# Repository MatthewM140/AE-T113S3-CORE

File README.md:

# AE-T113S3-CORE

A custom **Allwinner T113-S3 core board** designed to solder onto a carrier PCB. Revision **R1.0** uses a **35 × 35 mm** footprint with **100 castellated pads** around its four edges.

## Hardware at a glance

| Feature | Details |
| --- | --- |
| Processor | Allwinner T113-S3 |
| Storage | 256 MB NAND flash |
| Module footprint | 35 × 35 mm, 100 castellated pads |
| Carrier connections | GPIO, USB, SPI0, audio, TV out, reset, reference clock, 3.3 V and ground |
| I/O voltage selection | Solder jumpers marked **PG** (3.3 V / 1.8 V) and **PE** (3.3 V / 2.8 V) |

## Design files

| File | Contents |
| --- | --- |
| [KiCad project](T113-S3_Core_V1/T113-S3_Core_V1/T113-S3_Core_V1.kicad_pro) | Open this project to browse the schematic and PCB layout. |
| [Schematic](T113-S3_Core_V1/T113-S3_Core_V1/T113-S3_Core_V1.kicad_sch) | Circuit design and signal assignments. |
| [PCB layout](T113-S3_Core_V1/T113-S3_Core_V1/T113-S3_Core_V1.kicad_pcb) | Board outline, component placement, routing, and numbered pads. |
| [KiCad libraries](libraries/) | Custom symbols, footprints, and 3D models. |
| [Fabrication archive](T113-S3_Core_V1/T113-S3_Core_V1_FAB.zip) | Gerber and drill files. [Browse the unpacked files](T113-S3_Core_V1/T113-S3_Core_V1_FAB/). |

## Carrier board integration

Start with the [100-pad carrier landing footprint](libraries/footprints.pretty/Carrier_Landing_35x35_100P.kicad_mod) in the repository. Use the schematic and PCB layout to check pad numbering, the pin 1 orientation, and the PG and PE voltage selections against your carrier design.

## PCB routing and pad labels

Click the layout image to open it at full resolution.

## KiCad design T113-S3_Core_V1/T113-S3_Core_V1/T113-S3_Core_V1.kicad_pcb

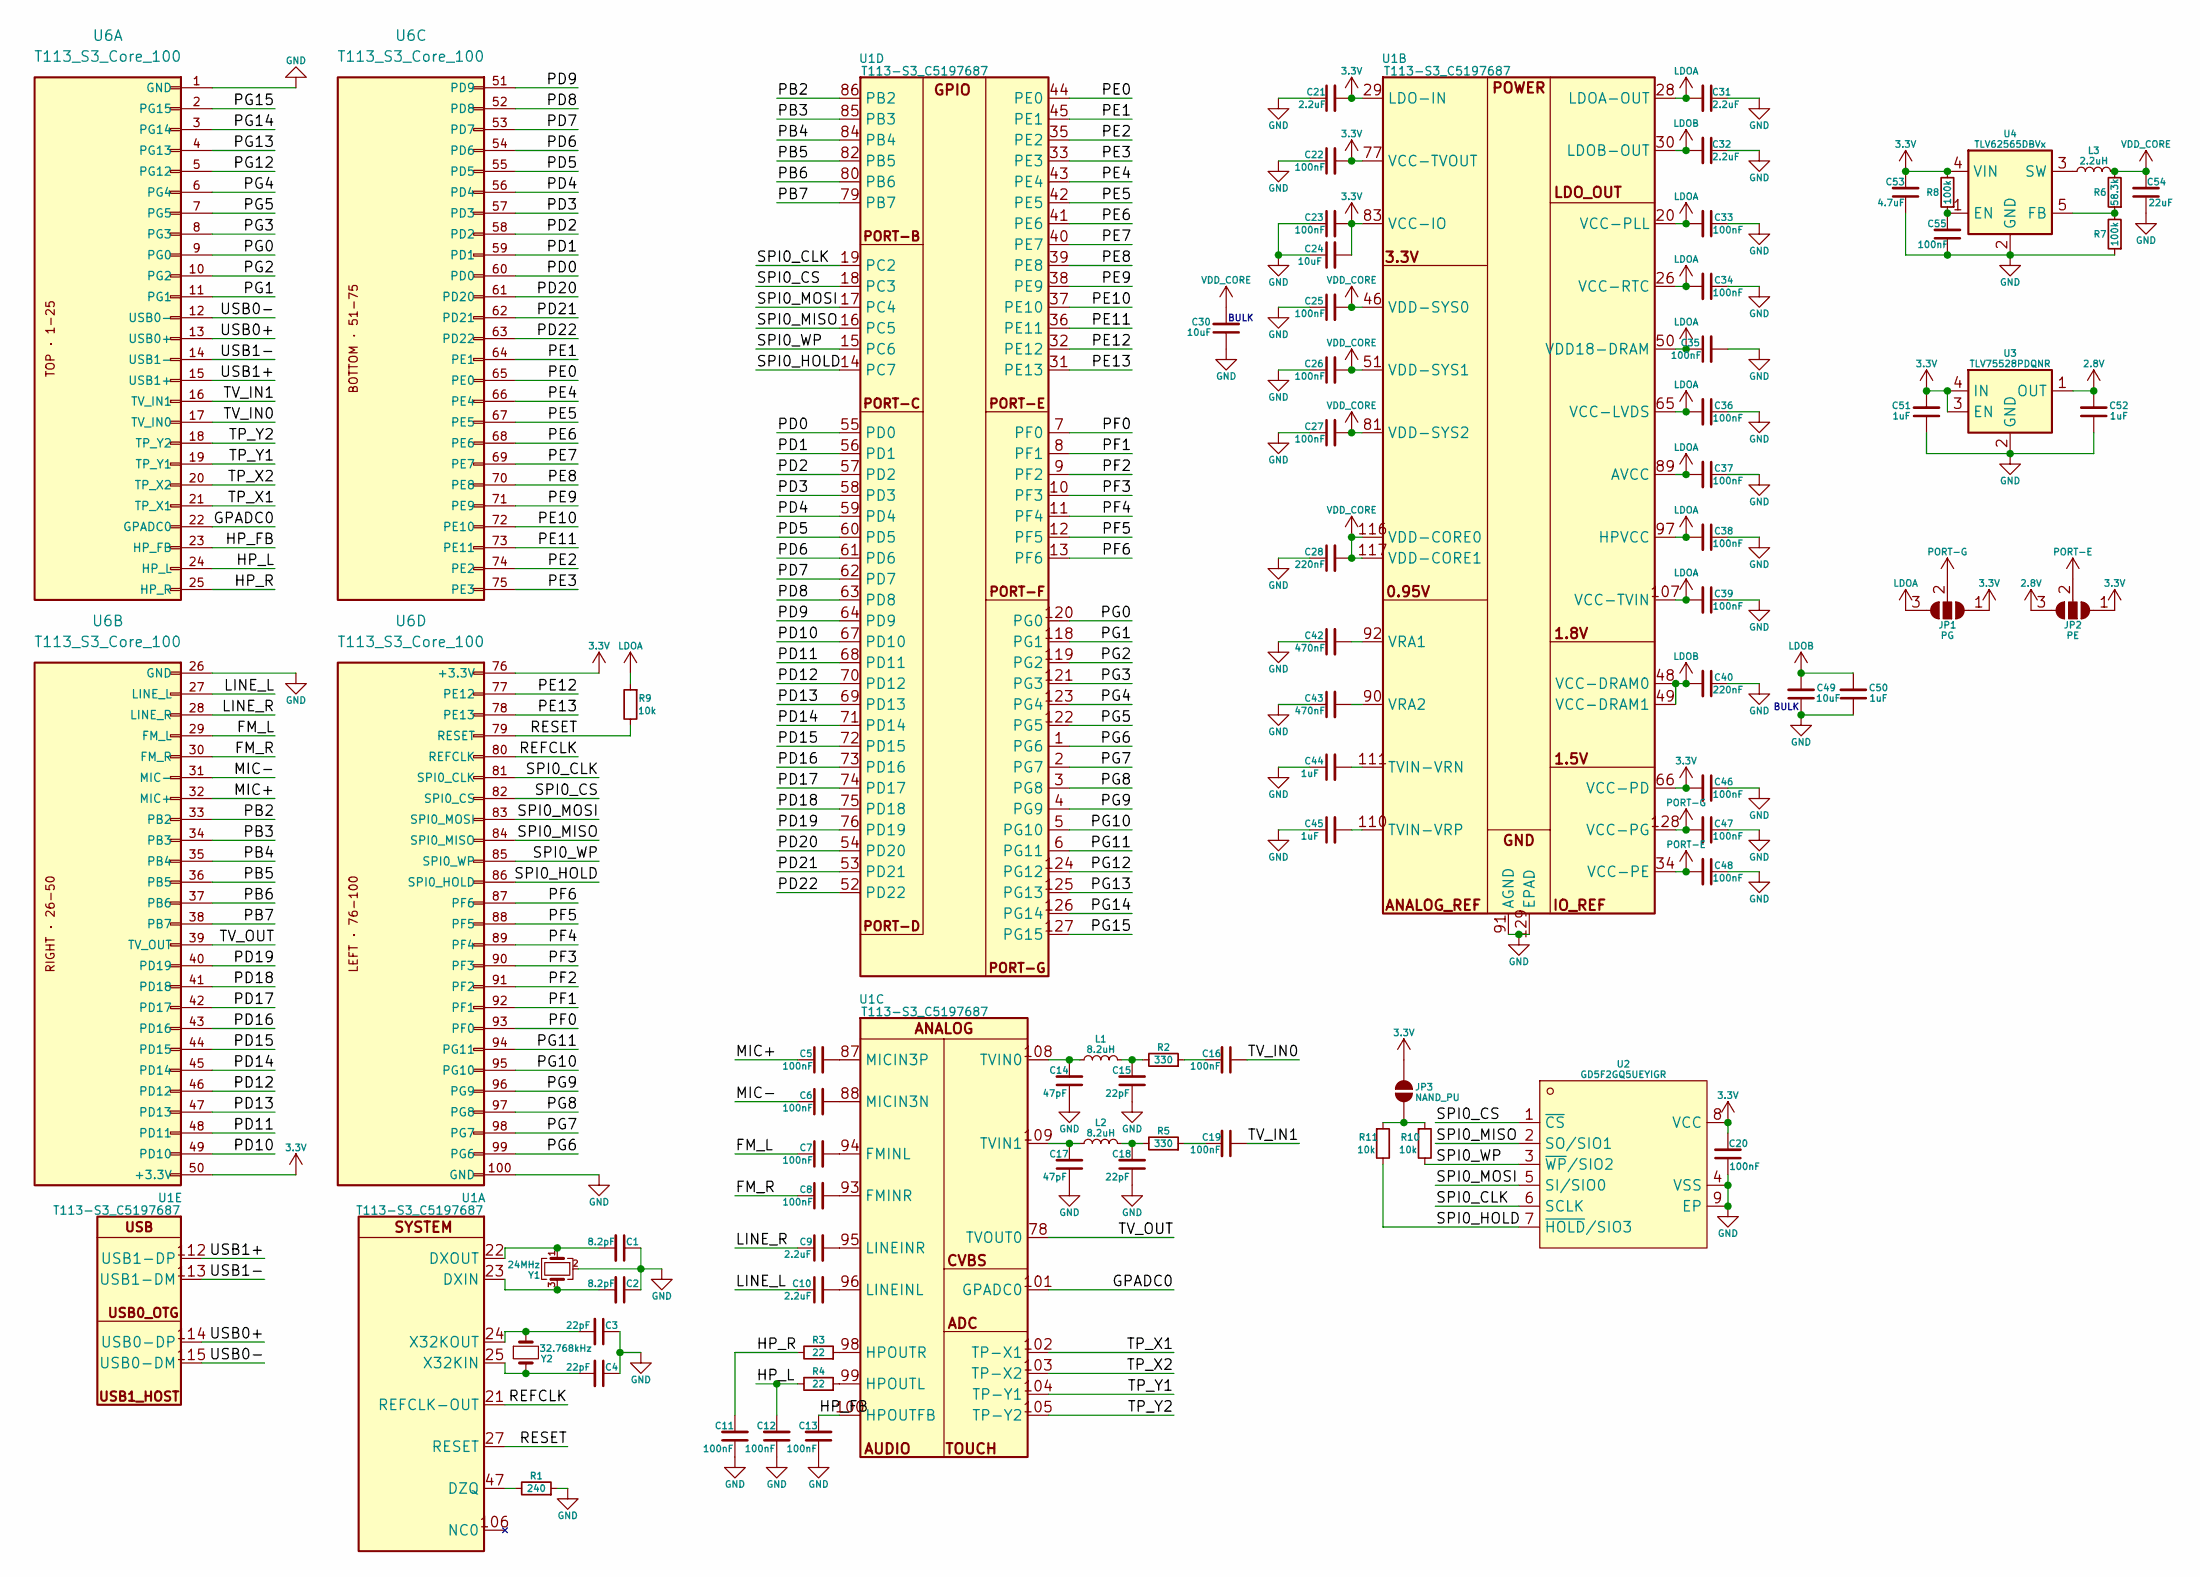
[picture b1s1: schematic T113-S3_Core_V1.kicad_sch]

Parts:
C1, C2: 8.2pF; C_0402_1005Metric
C3, C4, C15, C18: 22pF; C_0402_1005Metric
C5, C6, C7, C8, C11, C12, C13, C16, C19, C20, C22, C23, C25, C26, C27, C33, C34, C35, C36, C37, C38, C39, C46, C48, C55: 100nF; C_0402_1005Metric
C9, C10, C21, C31, C32: 2.2uF; C_0402_1005Metric
C14, C17: 47pF; C_0402_1005Metric
C24, C30, C49: 10uF; C_0603_1608Metric
C28, C40: 220nF; C_0402_1005Metric
C42, C43: 470nF; C_0402_1005Metric
C44, C45, C50, C51, C52: 1uF; C_0402_1005Metric
C47: 100nF; R_0201_0603Metric
C53: 4.7uF; C_0603_1608Metric
C54: 22uF; C_0603_1608Metric
JP1: PG; SolderJumper-3_P1.3mm_Open_RoundedPad1.0x1.5mm_NumberLabels
JP2: PE; SolderJumper-3_P1.3mm_Open_RoundedPad1.0x1.5mm_NumberLabels
JP3: NAND_PU; SolderJumper-2_P1.3mm_Open_RoundedPad1.0x1.5mm
L1, L2: 8.2uH; L_0603_1608Metric
L3: 2.2uH; F1C12016122R2M
R1: 240; R_0402_1005Metric
R2, R5: 330; R_0402_1005Metric
R3, R4: 22; R_0402_1005Metric
R6: 58.3k; R_0402_1005Metric
R7, R8: 100k; R_0402_1005Metric
R9, R10, R11: 10k; R_0402_1005Metric
U1: T113-S3_C5197687; LQFP-128_L14.0-W14.0-P0.40-LS16.0-BL-EP5.6; MPN T113-S3; LCSC Part C5197687
U2: GD5F2GQ5UEYIGR; WSON-8_L6.0-W8.0-P1.27-BL-EP; MPN GD5F2GQ5UEYIGR; LCSC Part C2880463
U3: TLV75528PDQNR; Texas_X2SON-4_1x1mm_P0.65mm; MPN TLV75528PDQNR; LCSC C2865384
U4: TLV62565DBVx; SOT-23-5
U6: T113_S3_Core_100; Module_Castellated_35x35_100P
Y1: 24MHz; Crystal_SMD_3225-4Pin_3.2x2.5mm
Y2: 32.768kHz; Crystal_SMD_MicroCrystal_CC7V-T1A-2Pin_3.2x1.5mm

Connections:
2.8V: C52.2, JP2.3 (B), U3.1 (OUT)
3.3V: C20.2, C21.2, C22.2, C23.2, C24.2, C46.2, C51.2, C53.2, JP1.1 (A), JP2.1 (A), JP3.2 (B), R8.2, U1.29 (LDO-IN), U1.66 (VCC-PD), U1.77 (VCC-TVOUT), U1.83 (VCC-IO), U2.8 (VCC), U3.3 (EN), U3.4 (IN), U4.4 (VIN), U6.50 (+3.3V), U6.76 (+3.3V)
/FM_L: C7.1, U6.29 (FM_L)
/FM_R: C8.1, U6.30 (FM_R)
/GPADC0: U1.101 (GPADC0), U6.22 (GPADC0)
/HP_FB: C13.2, U1.100 (HPOUTFB), U6.23 (HP_FB)
/HP_L: C12.2, R4.2, U6.24 (HP_L)
/HP_R: C11.2, R3.2, U6.25 (HP_R)
/LINE_L: C10.1, U6.27 (LINE_L)
/LINE_R: C9.1, U6.28 (LINE_R)
/MIC+: C5.1, U6.32 (MIC+)
/MIC-: C6.1, U6.31 (MIC-)
/PB2: U1.86 (PB2), U6.33 (PB2)
/PB3: U1.85 (PB3), U6.34 (PB3)
/PB4: U1.84 (PB4), U6.35 (PB4)
/PB5: U1.82 (PB5), U6.36 (PB5)
/PB6: U1.80 (PB6), U6.37 (PB6)
/PB7: U1.79 (PB7), U6.38 (PB7)
/PD0: U1.55 (PD0), U6.60 (PD0)
/PD1: U1.56 (PD1), U6.59 (PD1)
/PD2: U1.57 (PD2), U6.58 (PD2)
/PD3: U1.58 (PD3), U6.57 (PD3)
/PD4: U1.59 (PD4), U6.56 (PD4)
/PD5: U1.60 (PD5), U6.55 (PD5)
/PD6: U1.61 (PD6), U6.54 (PD6)
/PD7: U1.62 (PD7), U6.53 (PD7)
/PD8: U1.63 (PD8), U6.52 (PD8)
/PD9: U1.64 (PD9), U6.51 (PD9)
/PD10: U1.67 (PD10), U6.49 (PD10)
/PD11: U1.68 (PD11), U6.48 (PD11)
/PD12: U1.70 (PD12), U6.46 (PD12)
/PD13: U1.69 (PD13), U6.47 (PD13)
/PD14: U1.71 (PD14), U6.45 (PD14)
/PD15: U1.72 (PD15), U6.44 (PD15)
/PD16: U1.73 (PD16), U6.43 (PD16)
/PD17: U1.74 (PD17), U6.42 (PD17)
/PD18: U1.75 (PD18), U6.41 (PD18)
/PD19: U1.76 (PD19), U6.40 (PD19)
/PD20: U1.54 (PD20), U6.61 (PD20)
/PD21: U1.53 (PD21), U6.62 (PD21)
/PD22: U1.52 (PD22), U6.63 (PD22)
/PE0: U1.44 (PE0), U6.65 (PE0)
/PE1: U1.45 (PE1), U6.64 (PE1)
/PE2: U1.35 (PE2), U6.74 (PE2)
/PE3: U1.33 (PE3), U6.75 (PE3)
/PE4: U1.43 (PE4), U6.66 (PE4)
/PE5: U1.42 (PE5), U6.67 (PE5)
/PE6: U1.41 (PE6), U6.68 (PE6)
/PE7: U1.40 (PE7), U6.69 (PE7)
/PE8: U1.39 (PE8), U6.70 (PE8)
/PE9: U1.38 (PE9), U6.71 (PE9)
/PE10: U1.37 (PE10), U6.72 (PE10)
/PE11: U1.36 (PE11), U6.73 (PE11)
/PE12: U1.32 (PE12), U6.77 (PE12)
/PE13: U1.31 (PE13), U6.78 (PE13)
/PF0: U1.7 (PF0), U6.93 (PF0)
/PF1: U1.8 (PF1), U6.92 (PF1)
/PF2: U1.9 (PF2), U6.91 (PF2)
/PF3: U1.10 (PF3), U6.90 (PF3)
/PF4: U1.11 (PF4), U6.89 (PF4)
/PF5: U1.12 (PF5), U6.88 (PF5)
/PF6: U1.13 (PF6), U6.87 (PF6)
/PG0: U1.120 (PG0), U6.9 (PG0)
/PG1: U1.118 (PG1), U6.11 (PG1)
/PG2: U1.119 (PG2), U6.10 (PG2)
/PG3: U1.121 (PG3), U6.8 (PG3)
/PG4: U1.123 (PG4), U6.6 (PG4)
/PG5: U1.122 (PG5), U6.7 (PG5)
/PG6: U1.1 (PG6), U6.99 (PG6)
/PG7: U1.2 (PG7), U6.98 (PG7)
/PG8: U1.3 (PG8), U6.97 (PG8)
/PG9: U1.4 (PG9), U6.96 (PG9)
/PG10: U1.5 (PG10), U6.95 (PG10)
/PG11: U1.6 (PG11), U6.94 (PG11)
/PG12: U1.124 (PG12), U6.5 (PG12)
/PG13: U1.125 (PG13), U6.4 (PG13)
/PG14: U1.126 (PG14), U6.3 (PG14)
/PG15: U1.127 (PG15), U6.2 (PG15)
/REFCLK: U1.21 (REFCLK-OUT), U6.80 (REFCLK)
/RESET: R9.2, U1.27 (RESET), U6.79 (RESET)
/SPI0_CLK: U1.19 (PC2), U2.6 (SCLK), U6.81 (SPI0_CLK)
/SPI0_CS: U1.18 (PC3), U2.1 (~CS), U6.82 (SPI0_CS)
/SPI0_HOLD: R11.2, U1.14 (PC7), U2.7 (~HOLD/SIO3), U6.86 (SPI0_HOLD)
/SPI0_MISO: U1.16 (PC5), U2.2 (SO/SIO1), U6.84 (SPI0_MISO)
/SPI0_MOSI: U1.17 (PC4), U2.5 (SI/SIO0), U6.83 (SPI0_MOSI)
/SPI0_WP: R10.2, U1.15 (PC6), U2.3 (~WP/SIO2), U6.85 (SPI0_WP)
/TP_X1: U1.102 (TP-X1), U6.21 (TP_X1)
/TP_X2: U1.103 (TP-X2), U6.20 (TP_X2)
/TP_Y1: U1.104 (TP-Y1), U6.19 (TP_Y1)
/TP_Y2: U1.105 (TP-Y2), U6.18 (TP_Y2)
/TV_IN0: C16.1, U6.17 (TV_IN0)
/TV_IN1: C19.1, U6.16 (TV_IN1)
/TV_OUT: U1.78 (TVOUT0), U6.39 (TV_OUT)
/USB0+: U1.114 (USB0-DP), U6.13 (USB0+)
/USB0-: U1.115 (USB0-DM), U6.12 (USB0-)
/USB1+: U1.112 (USB1-DP), U6.15 (USB1+)
/USB1-: U1.113 (USB1-DM), U6.14 (USB1-)
GND: C1.1, C2.1, C3.1, C4.1, C11.1, C12.1, C13.1, C14.1, C15.1, C17.1, C18.1, C20.1, C21.1, C22.1, C23.1, C24.1, C25.1, C26.1, C27.1, C28.1, C30.1, C31.1, C32.1, C33.1, C34.1, C35.2, C36.1, C37.1, C38.1, C39.1, C40.1, C42.1, C43.1, C44.1, C45.1, C46.1, C47.1, C48.1, C49.1, C50.1, C51.1, C52.1, C53.1, C54.1, C55.1, R1.1, R7.1, U1.91 (AGND), U1.129 (EPAD), U2.4 (VSS), U2.9 (EP), U3.2 (GND), U3.5 (EP), U4.2 (GND), U6.1 (GND), U6.26 (GND), U6.100 (GND), Y1.2 (G), Y1.4 (G)
LDOA: C31.2, C33.2, C34.2, C35.1, C36.2, C37.2, C38.2, C39.2, JP1.3 (B), R9.1, U1.20 (VCC-PLL), U1.26 (VCC-RTC), U1.28 (LDOA-OUT), U1.50 (VDD18-DRAM), U1.65 (VCC-LVDS), U1.89 (AVCC), U1.97 (HPVCC), U1.107 (VCC-TVIN)
LDOB: C32.2, C40.2, C49.2, C50.2, U1.30 (LDOB-OUT), U1.48 (VCC-DRAM0), U1.49 (VCC-DRAM1)
unnamed: C15.2, L1.2, R2.2
unnamed: C16.2, R2.1
unnamed: C18.2, L2.2, R5.2
unnamed: C19.2, R5.1
unnamed: JP3.1 (A), R10.1, R11.1
unnamed: C2.2, U1.23 (DXIN), Y1.3
unnamed: C1.2, U1.22 (DXOUT), Y1.1
unnamed: R1.2, U1.47 (DZQ)
unnamed: C4.2, U1.25 (X32KIN), Y2.2
unnamed: C3.2, U1.24 (X32KOUT), Y2.1
unnamed: C44.2, U1.111 (TVIN-VRN)
unnamed: C45.2, U1.110 (TVIN-VRP)
unnamed: C42.2, U1.92 (VRA1)
unnamed: C43.2, U1.90 (VRA2)
unnamed: C7.2, U1.94 (FMINL)
unnamed: C8.2, U1.93 (FMINR)
unnamed: R4.1, U1.99 (HPOUTL)
unnamed: R3.1, U1.98 (HPOUTR)
unnamed: C10.2, U1.96 (LINEINL)
unnamed: C9.2, U1.95 (LINEINR)
unnamed: C6.2, U1.88 (MICIN3N)
unnamed: C5.2, U1.87 (MICIN3P)
unnamed: C14.2, L1.1, U1.108 (TVIN0)
unnamed: C17.2, L2.1, U1.109 (TVIN1)
unnamed: C55.2, R8.1, U4.1 (EN)
unnamed: R6.1, R7.2, U4.5 (FB)
unnamed: L3.1, U4.3 (SW)
PORT-E: C48.2, JP2.2 (C), U1.34 (VCC-PE)
PORT-G: C47.2, JP1.2 (C), U1.128 (VCC-PG)
VDD_CORE: C25.2, C26.2, C27.2, C28.2, C30.2, C54.2, L3.2, R6.2, U1.46 (VDD-SYS0), U1.51 (VDD-SYS1), U1.81 (VDD-SYS2), U1.116 (VDD-CORE0), U1.117 (VDD-CORE1)

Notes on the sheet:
BULK

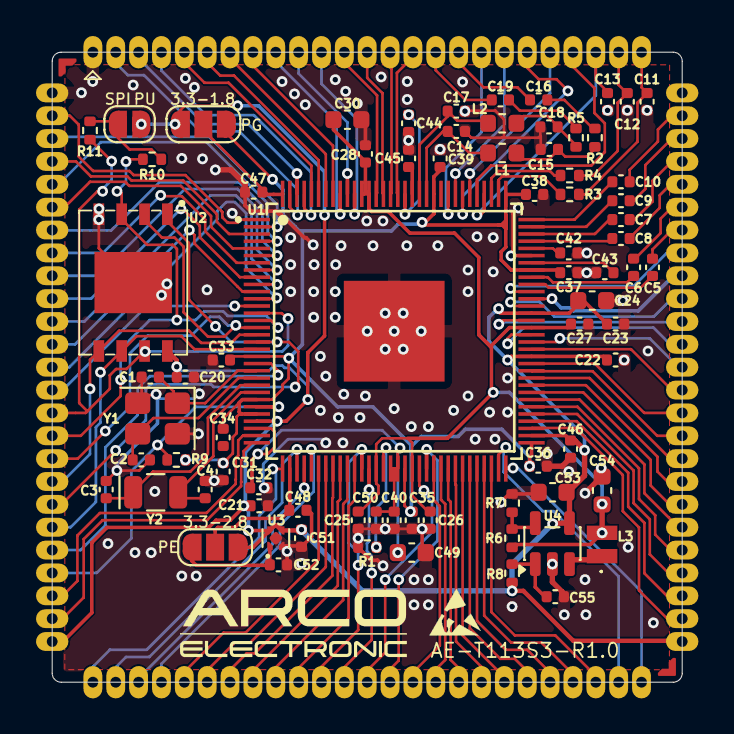
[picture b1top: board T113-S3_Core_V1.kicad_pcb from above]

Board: 2 copper layers, 35.0 x 35.0 mm, 77 parts (0 on the bottom side), 130 nets.
